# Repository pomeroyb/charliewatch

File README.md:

ChuckWatch
-----
This is a version of [OSResearch's excellent CharlieWatch](https://github.com/osresearch/charliewatch) with a bit more functionality. It adds an [LIS3DH](https://www.st.com/content/ccc/resource/technical/document/datasheet/3c/ae/50/85/d6/b1/46/fe/CD00274221.pdf/files/CD00274221.pdf/jcr:content/translations/en.CD00274221.pdf) accelerometer. This will eventually allow the watch to respond to taps, opening up possibilities for interaction and setting of time.

Original README
------

"Analog" watch with 60+12 Charlieplexed LEDs. Based on Travis Goodspeed's
GoodWatch21 schematic, using the CC430F5137IRGZR CPU, which doesn't
have the LCD controller of the CC430F6xxx in the GoodWatch. There are
also pads for a six pin EZfet cable with pogopins for programming or
serial communication.

v0.2 works, although it has no radio parts.  It is exactly 1 square inch
of PCB and should fit in a 38mm or 36mm case.

v0.1 works, although the radio parts have not been tested.  It is a slightly
larger board and fits in a 40mm case.

[Charliewtch schematic](datasheets/charliewatch.pdf)

Programming cable
-----

From the top of the v0.1 board:
* RST / TDIO
* RXD on programmer
* TXD on programmer
* VCC
* TST / TCK
* GND

v0.2:
* greem
* white
* blue
* purple
* gray
* black

There is also a four-wire setup that might simplify the wiring.
Travis documents it and the power consumption here:
https://github.com/travisgoodspeed/goodwatch/wiki/EnergyTrace

Bricked Launchpad
-----

If you brick your launchpad by running Energia under Linux, it will no
longer program the Charliewatch.  The other weirdness is that `tilib`
can detect the device, but can't write to it unless run as root.

Energy Trace
----
* `libmsp430.so`: https://dlbeer.co.nz/articles/slac460y/index.html
* https://github.com/carrotIndustries/energytrace-util
* Have to update path to `MSP430.h` from the `slac/DLL430_v3/include` directory

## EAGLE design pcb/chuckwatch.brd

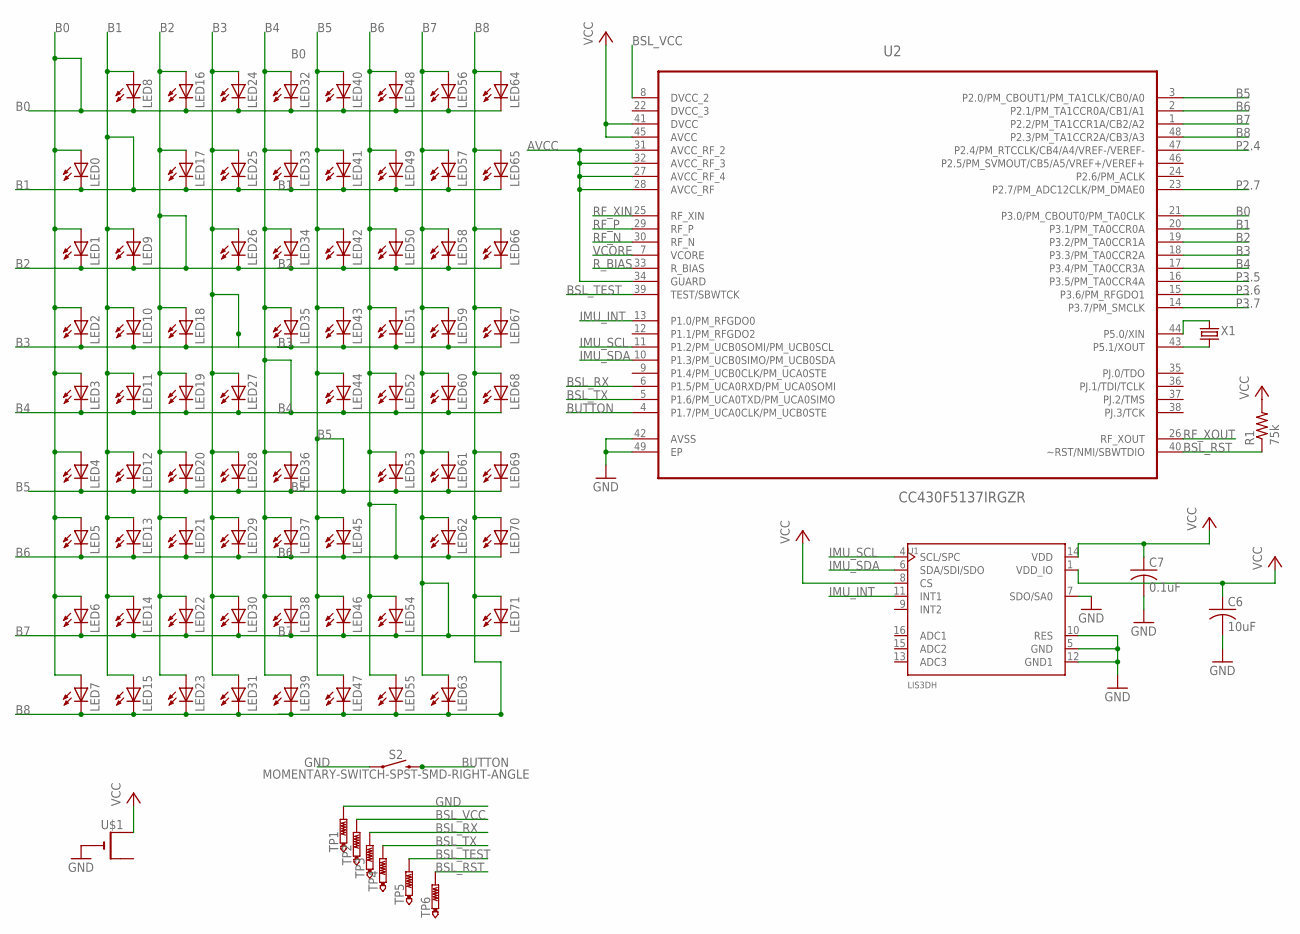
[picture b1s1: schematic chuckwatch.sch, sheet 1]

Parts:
C6: 10uF; C0603
C7: 0.1uF; C0603
LED0, LED1, LED2, LED3, LED4, LED5, LED6, LED7, LED8, LED9, LED10, LED11, LED12, LED13, LED14, LED15, LED16, LED17, LED18, LED19, LED20, LED21, LED22, LED23, LED24, LED25, LED26, LED27, LED28, LED29, LED30, LED31, LED32, LED33, LED34, LED35, LED36, LED37, LED38, LED39, LED40, LED41, LED42, LED43, LED44, LED45, LED46, LED47, LED48, LED49, LED50, LED51, LED52, LED53, LED54, LED55, LED56, LED57, LED58, LED59, LED60, LED61, LED62, LED63, LED64, LED65, LED66, LED67, LED68, LED69, LED70, LED71: LEDCHIPLED_0603; CHIPLED_0603
R1: 75k; R0402
S2: MOMENTARY-SWITCH-SPST-SMD-RIGHT-ANGLE; TACTILE_SWITCH_SMD_RIGHT_ANGLE
TP1: PTR1TP10SQ; TP10SQ
TP2, TP3, TP4, TP5, TP6: PTR1TP10R; TP10R
U1: LIS3DH; PQFN50P300X300X100-16N
U2: CC430F5137IRGZR; QFN50P700X700X100-49N
U$1: CR2032SMT; CR2032-SMD
X1: CRYSTALS-NOGND-IQXC-25; 2.0X1.2-2PAD

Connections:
AVCC: U2.27 (AVCC_RF_4), U2.28 (AVCC_RF), U2.31 (AVCC_RF_2), U2.32 (AVCC_RF_3), U2.34 (GUARD)
B0: LED0.A, LED1.A, LED2.A, LED3.A, LED4.A, LED5.A, LED6.A, LED7.A, LED8.C, LED16.C, LED24.C, LED32.C, LED40.C, LED48.C, LED56.C, LED64.C, U2.21 (P3.0/PM_CBOUT0/PM_TA0CLK)
B1: LED0.C, LED8.A, LED9.A, LED10.A, LED11.A, LED12.A, LED13.A, LED14.A, LED15.A, LED17.C, LED25.C, LED33.C, LED41.C, LED49.C, LED57.C, LED65.C, U2.20 (P3.1/PM_TA0CCR0A)
B2: LED1.C, LED9.C, LED16.A, LED17.A, LED18.A, LED19.A, LED20.A, LED21.A, LED22.A, LED23.A, LED26.C, LED34.C, LED42.C, LED50.C, LED58.C, LED66.C, U2.19 (P3.2/PM_TA0CCR1A)
B3: LED2.C, LED10.C, LED18.C, LED24.A, LED25.A, LED26.A, LED27.A, LED28.A, LED29.A, LED30.A, LED31.A, LED35.C, LED43.C, LED51.C, LED59.C, LED67.C, U2.18 (P3.3/PM_TA0CCR2A)
B4: LED3.C, LED11.C, LED19.C, LED27.C, LED32.A, LED33.A, LED34.A, LED35.A, LED36.A, LED37.A, LED38.A, LED39.A, LED44.C, LED52.C, LED60.C, LED68.C, U2.17 (P3.4/PM_TA0CCR3A)
B5: LED4.C, LED12.C, LED20.C, LED28.C, LED36.C, LED40.A, LED41.A, LED42.A, LED43.A, LED44.A, LED45.A, LED46.A, LED47.A, LED53.C, LED61.C, LED69.C, U2.3 (P2.0/PM_CBOUT1/PM_TA1CLK/CB0/A0)
B6: LED5.C, LED13.C, LED21.C, LED29.C, LED37.C, LED45.C, LED48.A, LED49.A, LED50.A, LED51.A, LED52.A, LED53.A, LED54.A, LED55.A, LED62.C, LED70.C, U2.2 (P2.1/PM_TA1CCR0A/CB1/A1)
B7: LED6.C, LED14.C, LED22.C, LED30.C, LED38.C, LED46.C, LED54.C, LED56.A, LED57.A, LED58.A, LED59.A, LED60.A, LED61.A, LED62.A, LED63.A, LED71.C, U2.1 (P2.2/PM_TA1CCR1A/CB2/A2)
B8: LED7.C, LED15.C, LED23.C, LED31.C, LED39.C, LED47.C, LED55.C, LED63.C, LED64.A, LED65.A, LED66.A, LED67.A, LED68.A, LED69.A, LED70.A, LED71.A, U2.48 (P2.3/PM_TA1CCR2A/CB3/A3)
BSL_RST: R1.1, TP6.TP, U2.40 (~RST/NMI/SBWTDIO)
BSL_RX: TP3.TP, U2.6 (P1.5/PM_UCA0RXD/PM_UCA0SOMI)
BSL_TEST: TP5.TP, U2.39 (TEST/SBWTCK)
BSL_TX: TP4.TP, U2.5 (P1.6/PM_UCA0TXD/PM_UCA0SIMO)
BSL_VCC: TP2.TP, U2.8 (DVCC_2)
BUTTON: S2.2, U2.4 (P1.7/PM_UCA0CLK/PM_UCB0STE)
DVCC_3: U2.22 (DVCC_3)
GND: C6.2, C7.2, S2.1, TP1.TP, U1.5 (GND), U1.7 (SDO/SA0), U1.10 (RES), U1.12 (GND1), U2.42 (AVSS), U2.49 (EP), U$1.-
IMU_INT: U1.11 (INT1), U2.13 (P1.0/PM_RFGDO0)
IMU_SCL: U1.4 (SCL/SPC), U2.11 (P1.2/PM_UCB0SOMI/PM_UCB0SCL)
IMU_SDA: U1.6 (SDA/SDI/SDO), U2.10 (P1.3/PM_UCB0SIMO/PM_UCB0SDA)
P2.4: U2.47 (P2.4/PM_RTCCLK/CB4/A4/VREF-/VEREF-)
P2.7: U2.23 (P2.7/PM_ADC12CLK/PM_DMAE0)
P3.5: U2.16 (P3.5/PM_TA0CCR4A)
P3.6: U2.15 (P3.6/PM_RFGDO1)
P3.7: U2.14 (P3.7/PM_SMCLK)
RF_N: U2.30 (RF_N)
RF_P: U2.29 (RF_P)
RF_XIN: U2.25 (RF_XIN)
RF_XOUT: U2.26 (RF_XOUT)
R_BIAS: U2.33 (R_BIAS)
VCC: C6.1, C7.1, R1.2, U1.1 (VDD_IO), U1.8 (CS), U1.14 (VDD), U2.41 (DVCC), U2.45 (AVCC), U$1.+$1 (+)
VCORE: U2.7 (VCORE)
XIN: U2.44 (P5.0/XIN), X1.2
XOUT: U2.43 (P5.1/XOUT), X1.1

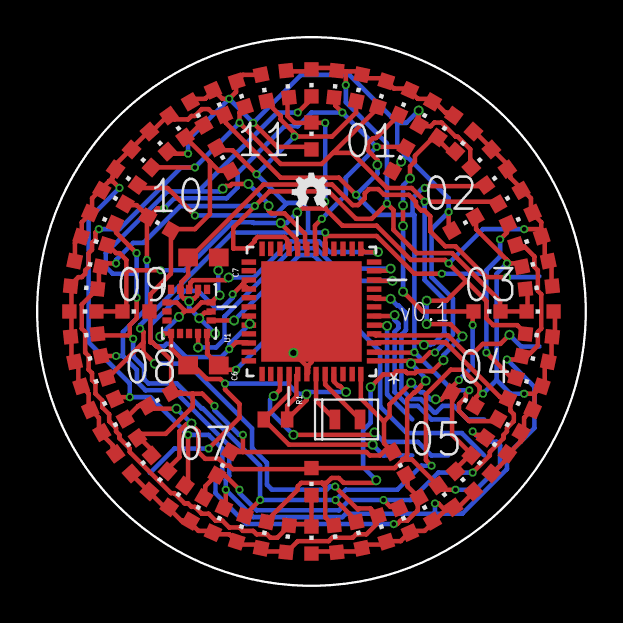
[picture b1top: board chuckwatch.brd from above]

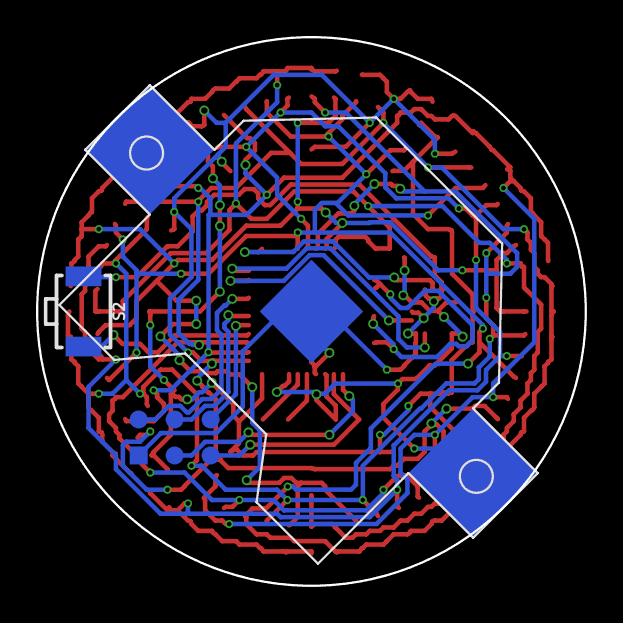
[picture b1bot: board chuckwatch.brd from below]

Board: 2 copper layers, 30.5 x 30.5 mm, 86 parts (8 on the bottom side), 23 nets.

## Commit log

2019-08-24 Add LIS3DH Accelerometer
    LIS3DH is an i2c accelerometer. Hope to use this to control the watch
    with tap based gestures
2019-08-24 Consolidate watch versions
    Removed everything older versions and version with RF (a feature not to
    be used in the foreseeable future)
2019-08-24 Cleaned up .brd File
    The Origin of the watch is (20, 20). Can now reference from that point
    when designing
2019-08-24 components place and laid out
2019-08-28 Place programming pins
    Also updated version to 0.3!
2019-09-09 Finish Routing
2019-09-09 Chuckwatch version 0.1

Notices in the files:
parts and their libraries:
SparkFun-Connectors: Licensing: Creative Commons ShareAlike 4.0 International - https://creativecommons.org/licenses/by-sa/4.0
